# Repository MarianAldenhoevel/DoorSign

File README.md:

# DoorSign
A PCB to be used as door sign.

* The board outline indicates the house number
* Silkscreen shows name and miscellanous information
* Mounting holes and hole for an illuminated ringer-button
* Footprints and layout to support a Raspberry Pi Pico (plain and W-version interchangeable), a LDR based light sensor, Neopixel LEDs and circuitry to detect a ringer-button press

Also firmware for the Pico to animate the LEDs suffering from feature-bloat. Guilty, pick a less capable chip next time.

Propably not useable directly by forking unless you happen to be me and live here. But if you find bits useful, go for it.

---
License:  
  
Creative Commons Attribution-ShareAlike  
CC BY-SA

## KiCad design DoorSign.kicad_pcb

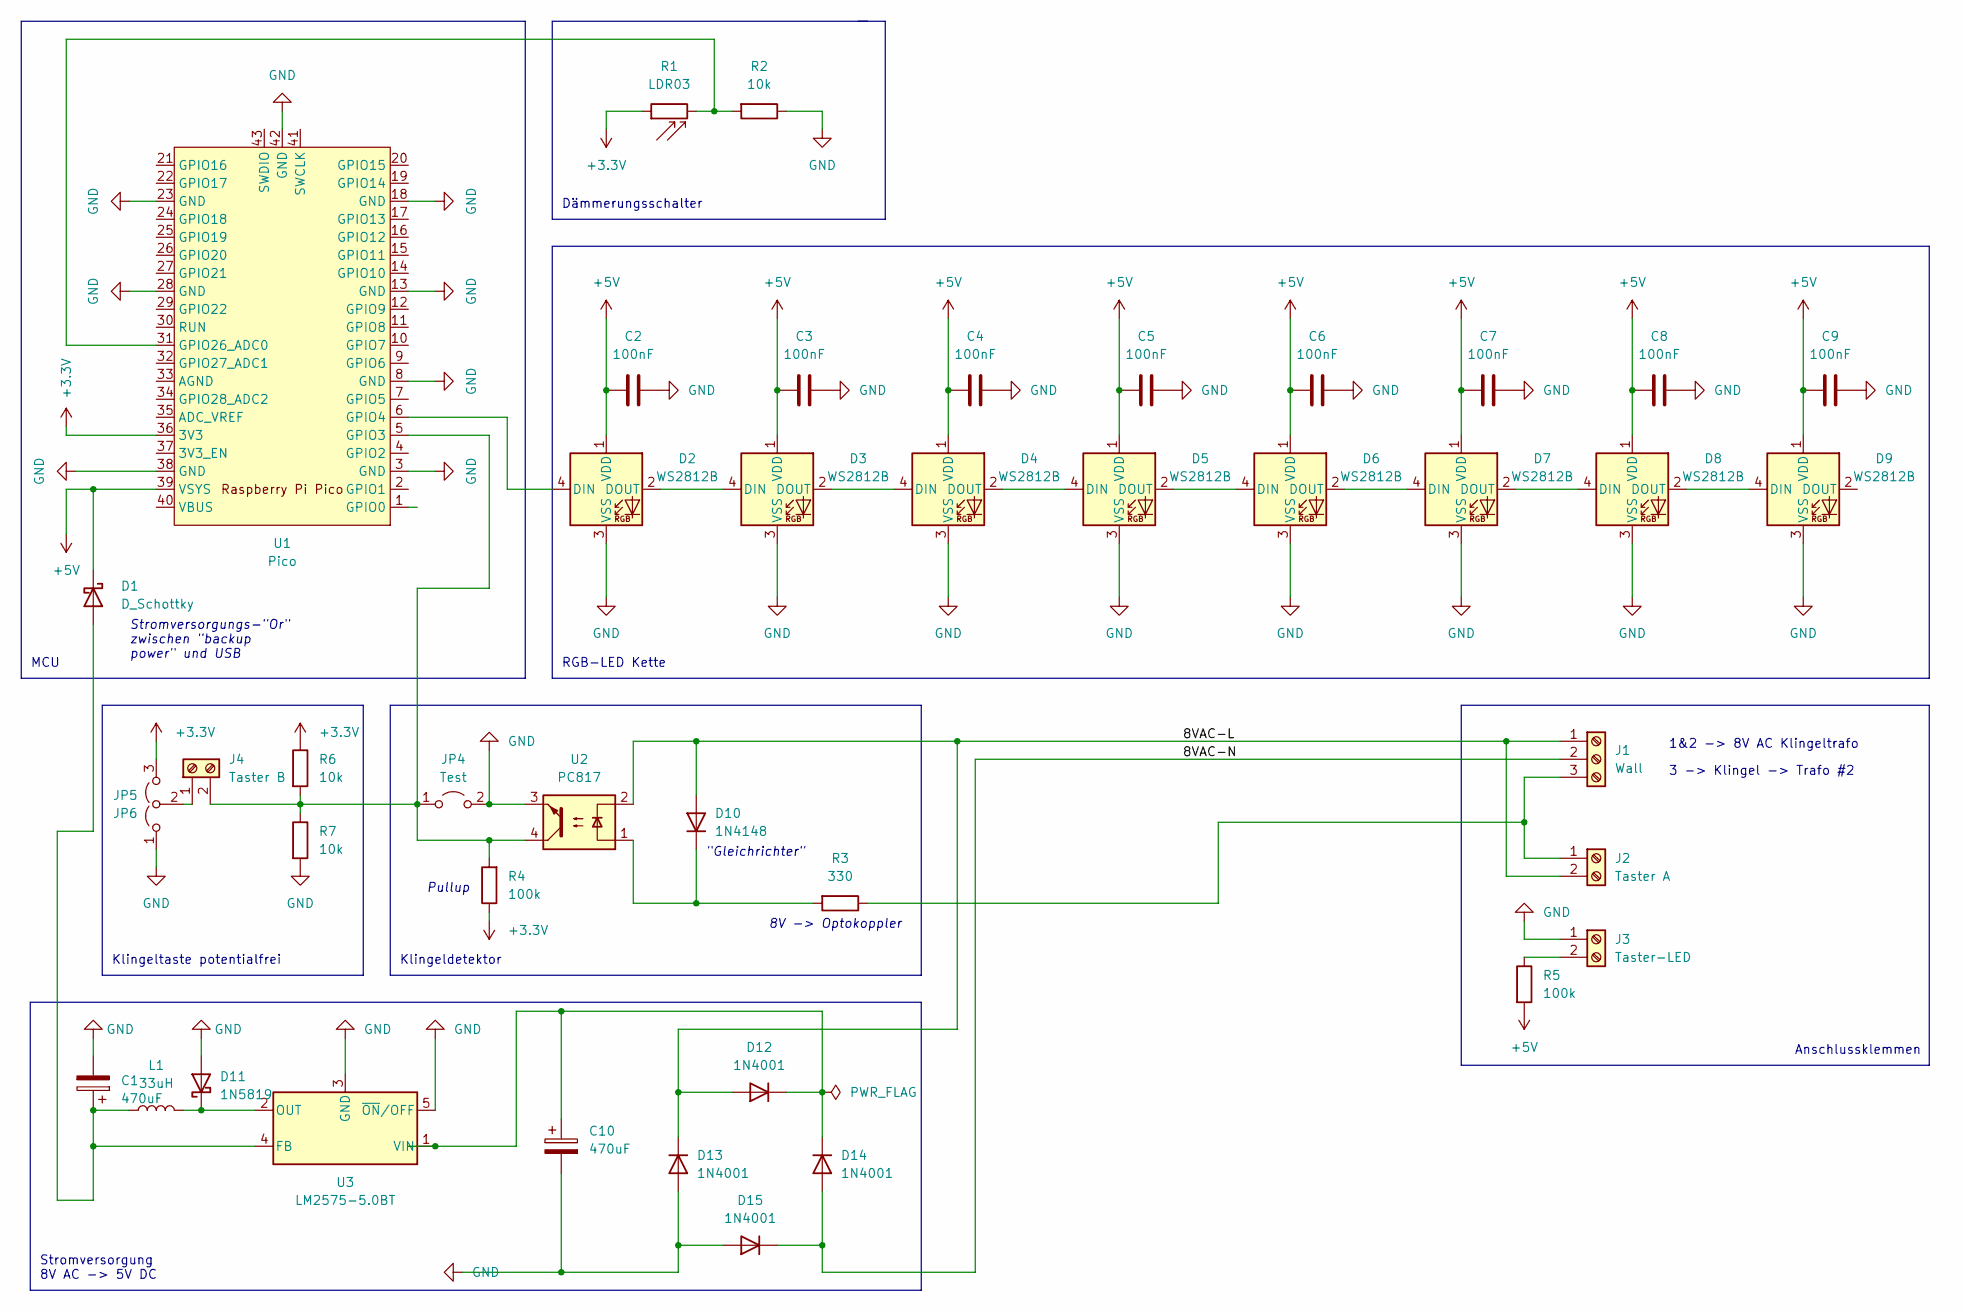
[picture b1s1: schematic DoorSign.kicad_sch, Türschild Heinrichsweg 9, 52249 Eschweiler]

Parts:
C1, C10: 470uF; CP_Radial_D12.5mm_P5.00mm
C2, C3, C4, C5, C6, C7, C8, C9: 100nF; C_0805_2012Metric_Pad1.18x1.45mm_HandSolder
D1: D_Schottky; D_DO-41_SOD81_P10.16mm_Horizontal
D2, D3, D4, D5, D6, D7, D8, D9: WS2812B; LED_WS2812B_PLCC4_5.0x5.0mm_P3.2mm
D10: 1N4148; D_DO-41_SOD81_P10.16mm_Horizontal
D11: 1N5819; D_DO-41_SOD81_P10.16mm_Horizontal
D12, D13, D14, D15: 1N4001; D_DO-41_SOD81_P10.16mm_Horizontal
J1: Wall; TerminalBlock_Altech_AK300-3_P5.00mm
J2: Taster A; TerminalBlock_Altech_AK300-2_P5.00mm
J3: Taster-LED; TerminalBlock_Altech_AK300-2_P5.00mm
J4: Taster B; TerminalBlock_Altech_AK300-2_P5.00mm
JP4: Test; PinHeader_1x02_P2.54mm_Vertical
JP5: JP6; PinHeader_1x03_P2.54mm_Vertical
L1: 33uH; L_Radial_D12.5mm_P7.00mm_Fastron_09HCP
R1: LDR03; R_LDR_10x8.5mm_P7.6mm_Vertical
R2, R6, R7: 10k; R_Axial_DIN0207_L6.3mm_D2.5mm_P15.24mm_Horizontal
R3: 330; R_Axial_DIN0207_L6.3mm_D2.5mm_P15.24mm_Horizontal
R4, R5: 100k; R_Axial_DIN0207_L6.3mm_D2.5mm_P15.24mm_Horizontal
U1: Pico; RPi_Pico_SMD_TH
U2: PC817; DIP-4_W7.62mm
U3: LM2575-5.0BT; TO-220-5_Vertical

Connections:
+3.3V: JP5.3 (B), R1.1, R4.1, R6.1, U1.36 (3V3)
+5V: C2.2, C3.2, C4.2, C5.2, C6.2, C7.2, C8.2, C9.2, D1.1 (K), D2.1 (VDD), D3.1 (VDD), D4.1 (VDD), D5.1 (VDD), D6.1 (VDD), D7.1 (VDD), D8.1 (VDD), D9.1 (VDD), R5.2, U1.39 (VSYS)
/8VAC-L: D10.2 (A), D12.2 (A), D13.1 (K), J1.1, J2.2, U2.2
/8VAC-N: D14.2 (A), D15.1 (K), J1.2
GND: C1.2, C2.1, C3.1, C4.1, C5.1, C6.1, C7.1, C8.1, C9.1, C10.2, D2.3 (VSS), D3.3 (VSS), D4.3 (VSS), D5.3 (VSS), D6.3 (VSS), D7.3 (VSS), D8.3 (VSS), D9.3 (VSS), D11.2 (A), D13.2 (A), D15.2 (A), J3.1, JP4.2 (B), JP5.1 (A), R2.1, R7.2, U1.3 (GND), U1.8 (GND), U1.13 (GND), U1.18 (GND), U1.23 (GND), U1.28 (GND), U1.38 (GND), U1.42 (GND), U2.3, U3.3 (GND), U3.5 (~ON/OFF)
unnamed: C1.1, D1.2 (A), L1.1, U3.4 (FB)
unnamed: C10.1, D12.1 (K), D14.1 (K), U3.1 (VIN)
unnamed: D2.2 (DOUT), D3.4 (DIN)
unnamed: D2.4 (DIN), U1.6 (GPIO4)
unnamed: D3.2 (DOUT), D4.4 (DIN)
unnamed: D4.2 (DOUT), D5.4 (DIN)
unnamed: D5.2 (DOUT), D6.4 (DIN)
unnamed: D6.2 (DOUT), D7.4 (DIN)
unnamed: D7.2 (DOUT), D8.4 (DIN)
unnamed: D8.2 (DOUT), D9.4 (DIN)
unnamed: D10.1 (K), R3.2, U2.1
unnamed: D11.1 (K), L1.2, U3.2 (OUT)
unnamed: J1.3, J2.1, R3.1
unnamed: J3.2, R5.1
unnamed: J4.1, JP5.2 (C)
unnamed: J4.2, JP4.1 (A), R4.2, R6.2, R7.1, U1.5 (GPIO3), U2.4
unnamed: R1.2, R2.2, U1.31 (GPIO26_ADC0)

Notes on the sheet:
Klingeltaste potentialfrei
RGB-LED Kette
Anschlussklemmen
1&2 -> 8V AC Klingeltrafo
8V -> Optokoppler
"Gleichrichter"
Stromversorgung 8V AC -> 5V DC
3 -> Klingel -> Trafo #2
Pullup
Klingeldetektor
MCU
Dämmerungsschalter
Stromversorgungs-"Or" zwischen "backup power" und USB

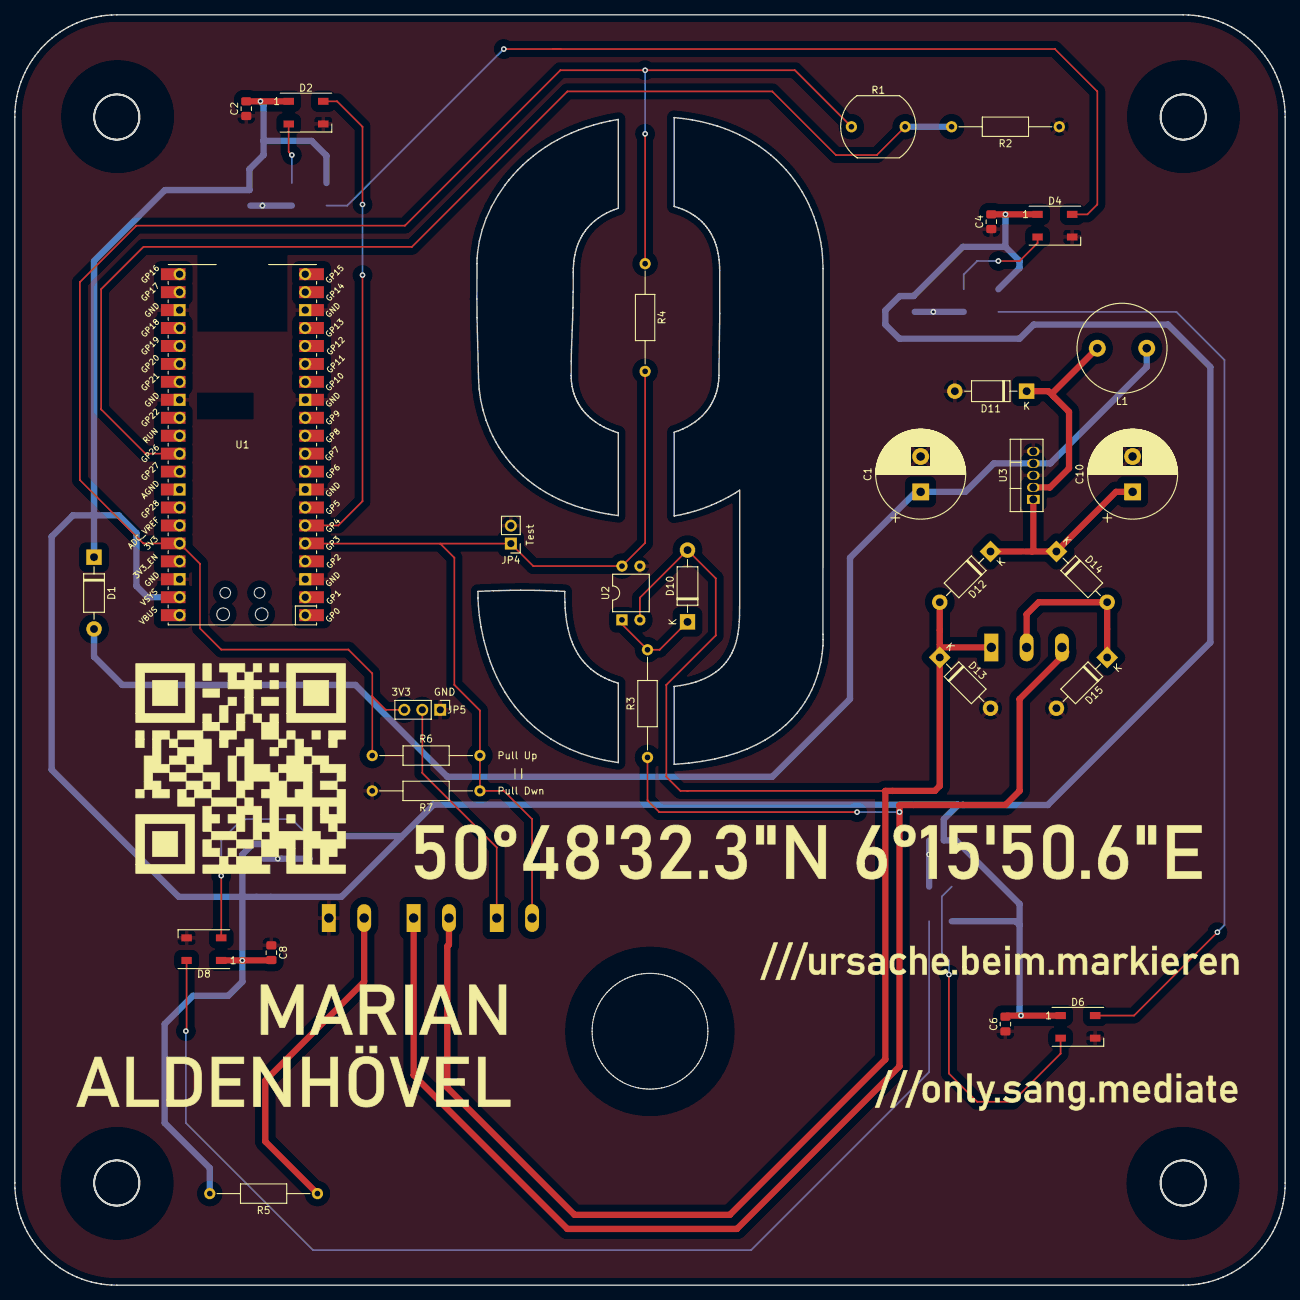
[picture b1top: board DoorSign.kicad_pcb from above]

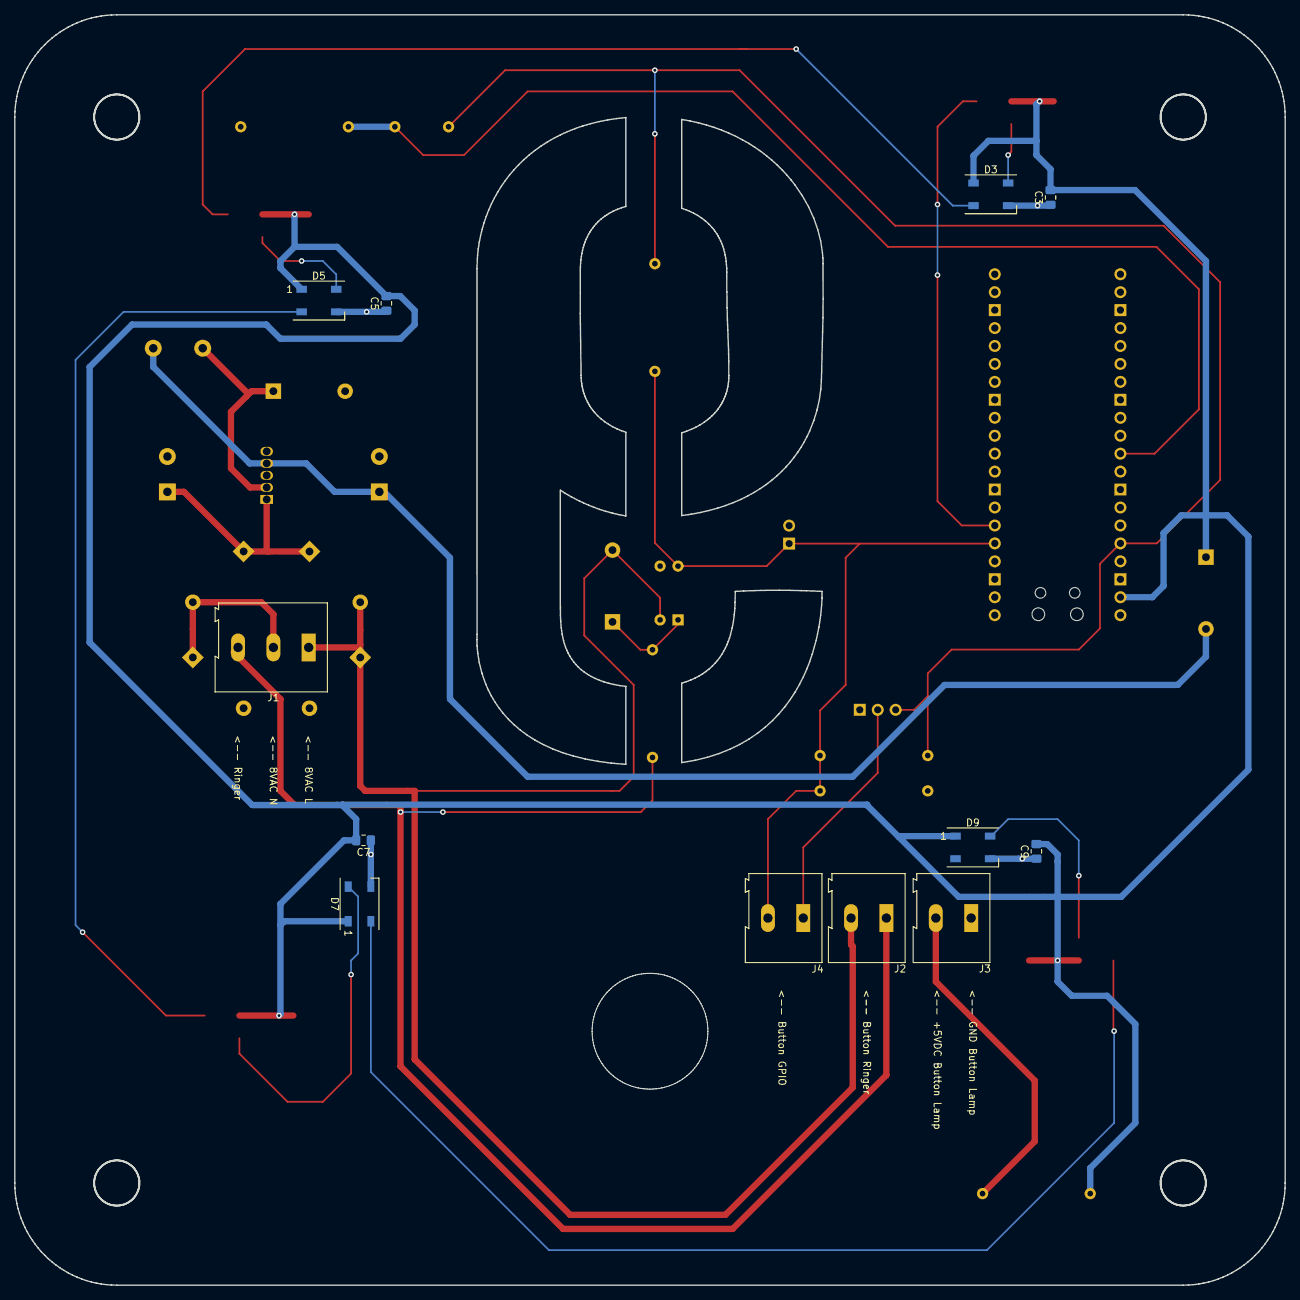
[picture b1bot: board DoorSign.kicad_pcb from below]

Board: 2 copper layers, 179.8 x 179.8 mm, 42 parts (12 on the bottom side), 22 nets.

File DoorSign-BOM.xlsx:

Ref | Qnty | Value | Cmp name | Footprint | Description | Vendor | Vendor-Code
C1, C10, | 2 | 470uF | C_Polarized | Capacitor_THT:CP_Radial_D12.5mm_P5.00mm | Polarized capacitor | Reichelt | FM-A 470U 35
C2, C3, C4, C5, C6, C7, C8, C9, | 8 | 100nF | C | Capacitor_SMD:C_0805_2012Metric_Pad1.18x1.45mm_HandSolder | Unpolarized capacitor | Reichelt | KEM Z5U0805 100N
D1, | 1 | D_Schottky | D_Schottky | Diode_THT:D_DO-41_SOD81_P10.16mm_Horizontal | Schottky diode | Reichelt | SB 1100
D2, D3, D4, D5, D6, D7, D8, D9, | 8 | WS2812B | WS2812B | LED_SMD:LED_WS2812B_PLCC4_5.0x5.0mm_P3.2mm | RGB LED with integrated controller
D10, | 1 | 1N4148 | 1N4148 | Diode_THT:D_DO-41_SOD81_P10.16mm_Horizontal | 100V 0.15A standard switching diode, DO-35 | Reichelt | 1N 4148
D11, | 1 | 1N5819 | 1N5819 | Diode_THT:D_DO-41_SOD81_P10.16mm_Horizontal | 40V 1A Schottky Barrier Rectifier Diode, DO-41 | Reichelt | 1N 5819
D12, D13, D14, D15, | 4 | 1N4001 | 1N4001 | Diode_THT:D_DO-41_SOD81_P10.16mm_Horizontal | 50V 1A General Purpose Rectifier Diode, DO-41 | Reichelt | 1N 4001
J1, | 1 | Wall | Screw_Terminal_01x03 | TerminalBlock:TerminalBlock_Altech_AK300-3_P5.00mm | Generic screw terminal, single row, 01x03, script generated (kicad-library-util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 | Reichelt | CTB5202-3
J2, | 1 | Taster | Screw_Terminal_01x02 | TerminalBlock:TerminalBlock_Altech_AK300-2_P5.00mm | Generic screw terminal, single row, 01x02, script generated (kicad-library-util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 | Reichelt | CTB5202-2
J3, | 1 | Taster-LED | Screw_Terminal_01x02 | TerminalBlock:TerminalBlock_Altech_AK300-2_P5.00mm | Generic screw terminal, single row, 01x02, script generated (kicad-library-util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 | Reichelt | CTB5202-2
L1, | 1 | 330uH | L | Inductor_THT:L_Axial_L5.0mm_D3.6mm_P10.00mm_Horizontal_Murata_BL01RN1A2A2 | Inductor | Reichelt | L-09HVP 330µ
R1, | 1 | LDR03 | LDR03 | OptoDevice:R_LDR_10x8.5mm_P7.6mm_Vertical | light dependent resistor | Conrad | 1762910 - NA
R2, | 1 | 10k | R | Resistor_THT:R_Axial_DIN0207_L6.3mm_D2.5mm_P15.24mm_Horizontal | Resistor | Reichelt | 1/4W 10K
R4, R5, | 2 | 100k | R | Resistor_THT:R_Axial_DIN0207_L6.3mm_D2.5mm_P15.24mm_Horizontal | Resistor | Reichelt | 1/4W 100K
R3, | 1 | 330 | R | Resistor_THT:R_Axial_DIN0207_L6.3mm_D2.5mm_P15.24mm_Horizontal | Resistor | Reichelt | 1/4W 330
U1, | 1 | Pico | Pico | MCU_RaspberryPi_and_Boards:RPi_Pico_SMD_TH | MCU | Reichelt | RASP PI PICO
U2, | 1 | PC817 | PC817 | Package_DIP:DIP-4_W7.62mm | DC Optocoupler, Vce 35V, CTR 50-300%, DIP-4 | Reichelt | LTV 817
U3, | 1 | LM2575-5.0BT | LM2575-5.0BT | Package_TO_SOT_THT:TO-220-5_Vertical | Fixed 5.0V 52kHz Simple 1A Buck Regulator, TO-220-5 | Reichelt | LM2575T-5G

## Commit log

2022-09-19 Initial import
2022-09-19 Ignores
2022-09-21 Added BOM and partial schematics
2022-10-05 added jumper for optocoupler
2022-10-05 connected all GND pins on the Pico
2022-10-05 Attempt to fix ERC message
2022-10-21 Rewired GPIOs for compatibility with Raspberry Pi Pico W
2022-10-21 Modified footprints for compatibility with Pi Pico W
2022-11-04 Potential free contactor and pull-up/down added
2022-11-04 Jumpers for potential free contact
2022-11-24 Added Pico Firmware
2022-11-25 Cleanup and implementation of animation
2022-11-25 Repair after FS crash
2022-11-25 Cleanup
2022-11-26 Cleanup, comments, spelling, refactoring
2022-11-26 Fixes after refactoring. Support for hardware WDT
2022-11-26 Blend in HSV space
2022-11-26 RTC support and ntp client
2022-11-26 Support for re-enabling animation remotely
2022-11-26 API and UI to switch animation
2022-11-27 Implemented RecursiveLock, more API endpoints
2022-11-27 added title image
2022-11-27 fixed title image
2022-11-27 added kicad.png
2022-11-27 save space
2022-11-27 Tests, debugging and fixes
2022-11-27 Gamma-correction
2022-11-27 log to file and logfile rotation
2022-11-27 Option to disable logging to file
2022-11-28 Testing, optimization
2022-11-29 Upload-script, Uptime, Status panel
2022-11-29 Misc small tweaks
